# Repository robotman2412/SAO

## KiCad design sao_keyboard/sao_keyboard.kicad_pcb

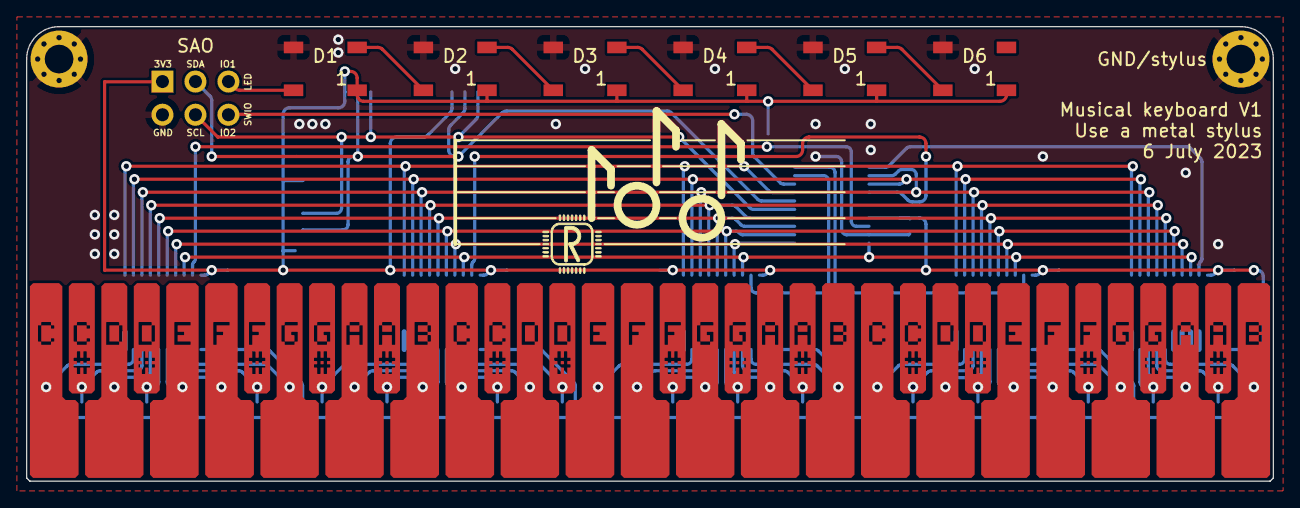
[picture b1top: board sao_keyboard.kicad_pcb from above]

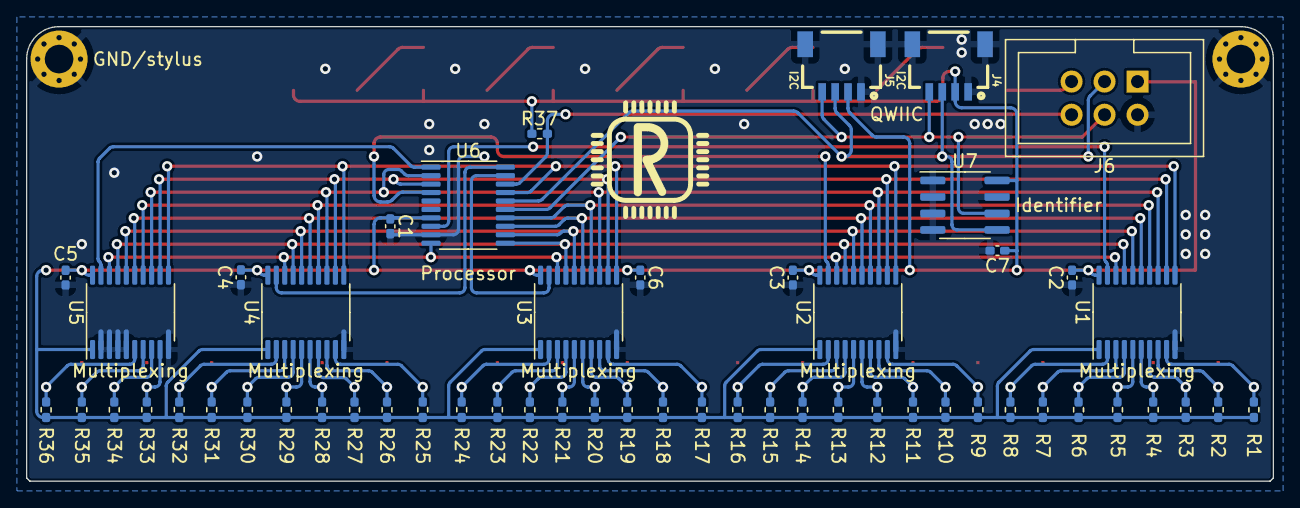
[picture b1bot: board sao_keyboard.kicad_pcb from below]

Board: 2 copper layers, 96.0 x 35.0 mm, 67 parts (54 on the bottom side), 60 nets.

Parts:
C1, C2, C3, C4, C5, C6, C7: 100n; C_0402_1005Metric_Pad0.74x0.62mm_HandSolder
D1, D2, D3, D4, D5, D6: WS2812B; LED_WS2812B_PLCC4_5.0x5.0mm_P3.2mm
G1: RobotMan2412_10mm
G2: RobotMan2412_5mm
H1, H2: MountingHole_Pad; MountingHole_2.2mm_M2_Pad_Via
J1, J2, J3: keyboard_32x15mm_p4mm_cu_label
J4, J5: I2C; 1X04_1MM_RA_GND
J6: sao_v2_addon_tht
R1, R2, R3, R4, R5, R6, R7, R8, R9, R10, R11, R12, R13, R14, R15, R16, R17, R18, R19, R20, R21, R22, R23, R24, R25, R26, R27, R28, R29, R30, R31, R32, R33, R34, R35, R36, R37: 1K; R_0402_1005Metric_Pad0.72x0.64mm_HandSolder
U1, U2, U3, U4, U5: 74LS245; TSSOP-20_4.4x6.5mm_P0.65mm
U6: CH32V003F4P6; TSSOP-20_4.4x6.5mm_P0.65mm
U7: 24LC00; SOIC-8_3.9x4.9mm_P1.27mm

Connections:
+3V3: C1.1, C2.1, C3.1, C4.1, C5.1, C6.1, C7.1, D1.1 (VDD), D2.1 (VDD), D3.1 (VDD), D4.1 (VDD), D5.1 (VDD), D6.1 (VDD), J4.2 (VCC), J5.2 (VCC), J6.1 (3V3), R1.1, R2.1, R3.1, R4.1, R5.1, R6.1, R7.1, R8.1, R9.1, R10.1, R11.1, R12.1, R13.1, R14.1, R15.1, R16.1, R17.1, R18.1, R19.1, R20.1, R21.1, R22.1, R23.1, R24.1, R25.1, R26.1, R27.1, R28.1, R29.1, R30.1, R31.1, R32.1, R33.1, R34.1, R35.1, R36.1, R37.1, U1.1 (A->B), U1.20 (VCC), U2.1 (A->B), U2.20 (VCC), U3.1 (A->B), U3.20 (VCC), U4.1 (A->B), U4.20 (VCC), U5.1 (A->B), U5.20 (VCC), U6.7 (VSS), U7.8 (VCC)
GND: C1.2, C2.2, C3.2, C4.2, C5.2, C6.2, C7.2, D1.3 (VSS), D2.3 (VSS), D3.3 (VSS), D4.3 (VSS), D5.3 (VSS), D6.3 (VSS), H1.1, H2.1, J4.1 (GND), J4.5, J4.6, J5.1 (GND), J5.5, J5.6, J6.2 (GND), U1.10 (GND), U2.10 (GND), U3.10 (GND), U4.10 (GND), U5.2 (A0), U5.3 (A1), U5.4 (A2), U5.5 (A3), U5.10 (GND), U6.9 (VDD), U7.1 (A0), U7.2 (A1), U7.3 (A2), U7.4 (GND), U7.7 (WP)
LED_DIN: D1.4 (DIN), J6.5 (IO1)
unnamed: D1.2 (DOUT), D2.4 (DIN)
unnamed: D2.2 (DOUT), D3.4 (DIN)
unnamed: D3.2 (DOUT), D4.4 (DIN)
unnamed: D4.2 (DOUT), D5.4 (DIN)
unnamed: D5.2 (DOUT), D6.4 (DIN)
SCL: J4.4 (SCL), J5.4 (SCL), J6.4 (SCL), U6.15 (PC5), U7.6 (SCL)
SDA: J4.3 (SDA), J5.3 (SDA), J6.3 (SDA), U6.16 (PC6), U7.5 (SDA)
SWIO: J6.6 (IO2), R37.2, U6.18 (PD1)
X0: U1.19 (CE), U6.8 (PD0)
X0Y0: J1.1 (C), R1.2, U1.9 (A7)
X0Y1: J1.2 (C#), R2.2, U1.8 (A6)
X0Y2: J1.3 (D), R3.2, U1.7 (A5)
X0Y3: J1.4 (D#), R4.2, U1.6 (A4)
X0Y4: J1.5 (E), R5.2, U1.5 (A3)
X0Y5: J1.6 (F), R6.2, U1.4 (A2)
X0Y6: J1.7 (F#), R7.2, U1.3 (A1)
X0Y7: J1.8 (G), R8.2, U1.2 (A0)
X1: U2.19 (CE), U6.4 (PD7)
X1Y0: J1.9 (G#), R9.2, U2.9 (A7)
X1Y1: J1.10 (A), R10.2, U2.8 (A6)
X1Y2: J1.11 (A#), R11.2, U2.7 (A5)
X1Y3: J1.12 (B), R12.2, U2.6 (A4)
X1Y4: J2.1 (C), R13.2, U2.5 (A3)
X1Y5: J2.2 (C#), R14.2, U2.4 (A2)
X1Y6: J2.3 (D), R15.2, U2.3 (A1)
X1Y7: J2.4 (D#), R16.2, U2.2 (A0)
X2: U3.19 (CE), U6.19 (PD2)
X2Y0: J2.5 (E), R17.2, U3.9 (A7)
X2Y1: J2.6 (F), R18.2, U3.8 (A6)
X2Y2: J2.7 (F#), R19.2, U3.7 (A5)
X2Y3: J2.8 (G), R20.2, U3.6 (A4)
X2Y4: J2.9 (G#), R21.2, U3.5 (A3)
X2Y5: J2.10 (A), R22.2, U3.4 (A2)
X2Y6: J2.11 (A#), R23.2, U3.3 (A1)
X2Y7: J2.12 (B), R24.2, U3.2 (A0)
X3: U4.19 (CE), U6.20 (PD3)
X3Y0: J3.1 (C), R25.2, U4.9 (A7)
X3Y1: J3.2 (C#), R26.2, U4.8 (A6)
X3Y2: J3.3 (D), R27.2, U4.7 (A5)
X3Y3: J3.4 (D#), R28.2, U4.6 (A4)
X3Y4: J3.5 (E), R29.2, U4.5 (A3)
X3Y5: J3.6 (F), R30.2, U4.4 (A2)
X3Y6: J3.7 (F#), R31.2, U4.3 (A1)
X3Y7: J3.8 (G), R32.2, U4.2 (A0)
X4: U5.19 (CE), U6.1 (PD4)
X4Y0: J3.9 (G#), R33.2, U5.9 (A7)
X4Y1: J3.10 (A), R34.2, U5.8 (A6)
X4Y2: J3.11 (A#), R35.2, U5.7 (A5)
X4Y3: J3.12 (B), R36.2, U5.6 (A4)
Y0: U1.11 (B7), U2.11 (B7), U3.11 (B7), U4.11 (B7), U5.11 (B7), U6.17 (PC7)
Y1: U1.12 (B6), U2.12 (B6), U3.12 (B6), U4.12 (B6), U5.12 (B6), U6.3 (PD6)
Y2: U1.13 (B5), U2.13 (B5), U3.13 (B5), U4.13 (B5), U5.13 (B5), U6.2 (PD5)
Y3: U1.14 (B4), U2.14 (B4), U3.14 (B4), U4.14 (B4), U5.14 (B4), U6.14 (PC4)
Y4: U1.15 (B3), U2.15 (B3), U3.15 (B3), U4.15 (B3), U5.15 (B3), U6.13 (PC3)
Y5: U1.16 (B2), U2.16 (B2), U3.16 (B2), U4.16 (B2), U5.16 (B2), U6.12 (PC2)
Y6: U1.17 (B1), U2.17 (B1), U3.17 (B1), U4.17 (B1), U5.17 (B1), U6.11 (PC1)
Y7: U1.18 (B0), U2.18 (B0), U3.18 (B0), U4.18 (B0), U5.18 (B0), U6.10 (PC0)

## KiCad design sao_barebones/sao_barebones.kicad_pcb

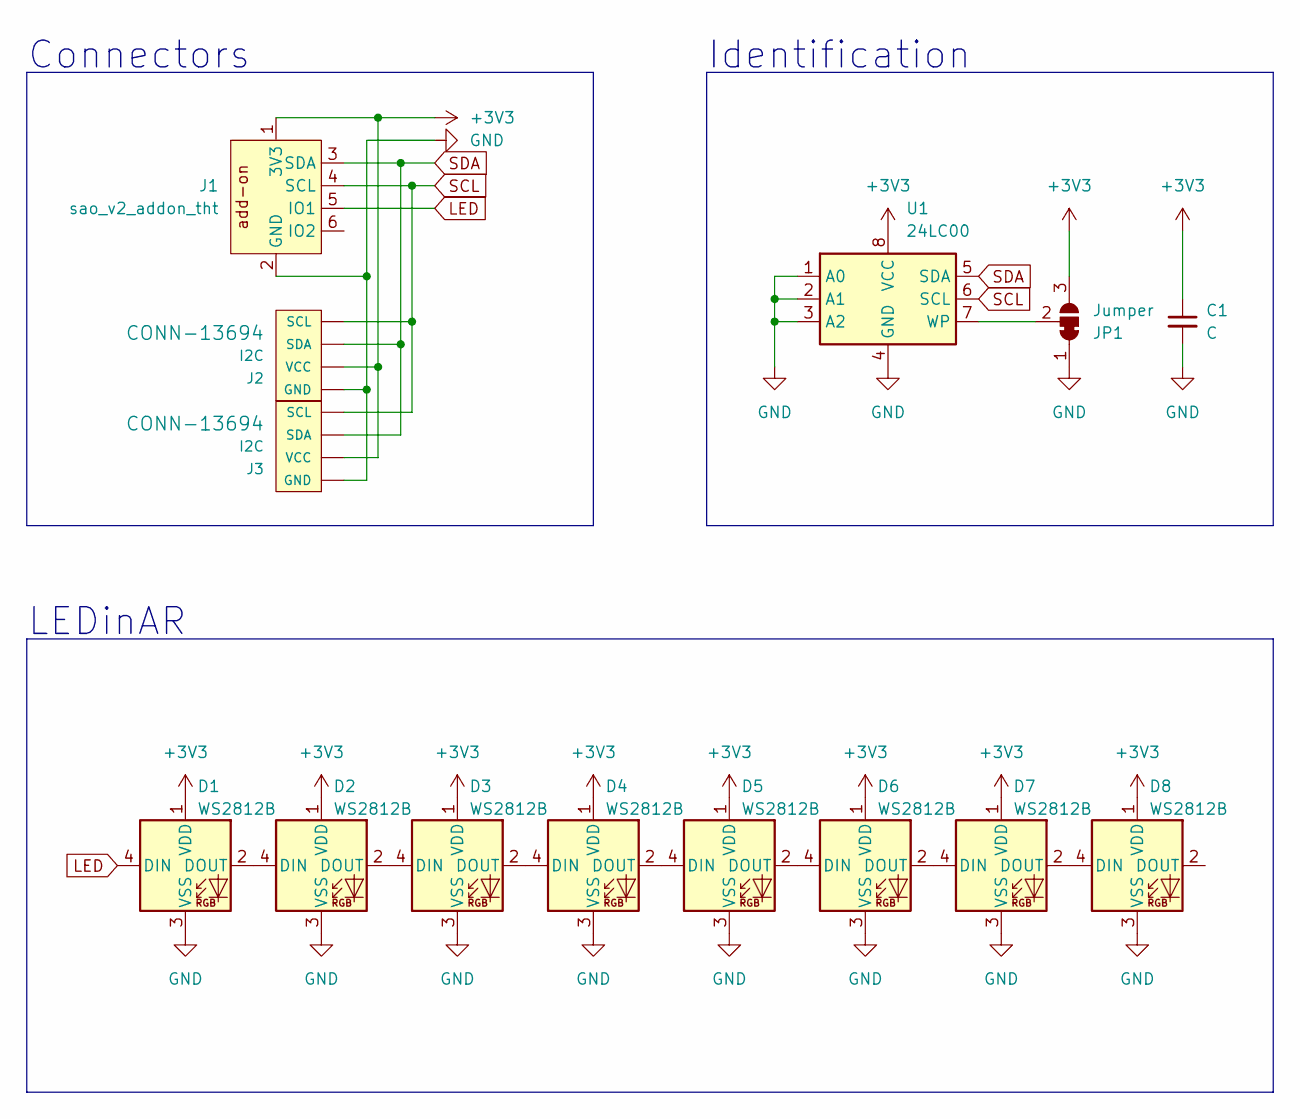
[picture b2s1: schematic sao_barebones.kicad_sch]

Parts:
C1: C; C_0402_1005Metric_Pad0.74x0.62mm_HandSolder
D1, D2, D3, D4, D5, D6, D7, D8: WS2812B; LED_WS2812B_PLCC4_5.0x5.0mm_P3.2mm
J1: sao_v2_addon_tht
J2, J3: I2C; 1X04_1MM_RA_GND; MPN SM04B-SRSS-TB; LCSC C160404
JP1: Jumper; SolderJumper-3_P1.3mm_Bridged12_RoundedPad1.0x1.5mm
U1: 24LC00; SOIC-8_3.9x4.9mm_P1.27mm

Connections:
+3V3: C1.1, D1.1 (VDD), D2.1 (VDD), D3.1 (VDD), D4.1 (VDD), D5.1 (VDD), D6.1 (VDD), D7.1 (VDD), D8.1 (VDD), J1.1 (3V3), J2.2 (VCC), J3.2 (VCC), JP1.3 (B), U1.8 (VCC)
GND: C1.2, D1.3 (VSS), D2.3 (VSS), D3.3 (VSS), D4.3 (VSS), D5.3 (VSS), D6.3 (VSS), D7.3 (VSS), D8.3 (VSS), J1.2 (GND), J2.1 (GND), J2.5, J2.6, J3.1 (GND), J3.5, J3.6, JP1.1 (A), U1.1 (A0), U1.2 (A1), U1.3 (A2), U1.4 (GND)
LED: D1.4 (DIN), J1.5 (IO1)
unnamed: D1.2 (DOUT), D2.4 (DIN)
unnamed: D2.2 (DOUT), D3.4 (DIN)
unnamed: D3.2 (DOUT), D4.4 (DIN)
unnamed: D4.2 (DOUT), D5.4 (DIN)
unnamed: D5.2 (DOUT), D6.4 (DIN)
unnamed: D6.2 (DOUT), D7.4 (DIN)
unnamed: D7.2 (DOUT), D8.4 (DIN)
unnamed: JP1.2 (C), U1.7 (WP)
SCL: J1.4 (SCL), J2.4 (SCL), J3.4 (SCL), U1.6 (SCL)
SDA: J1.3 (SDA), J2.3 (SDA), J3.3 (SDA), U1.5 (SDA)

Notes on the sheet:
Connectors
LEDinAR
Identification

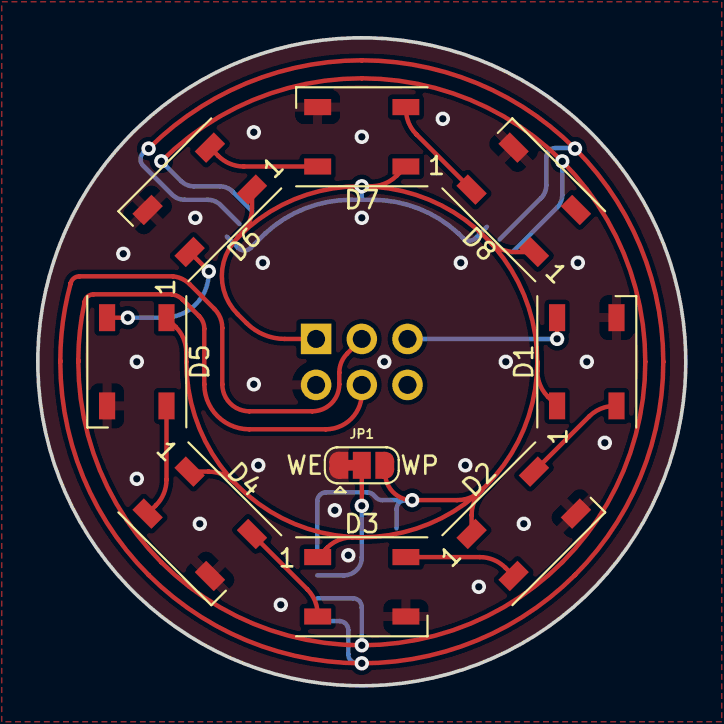
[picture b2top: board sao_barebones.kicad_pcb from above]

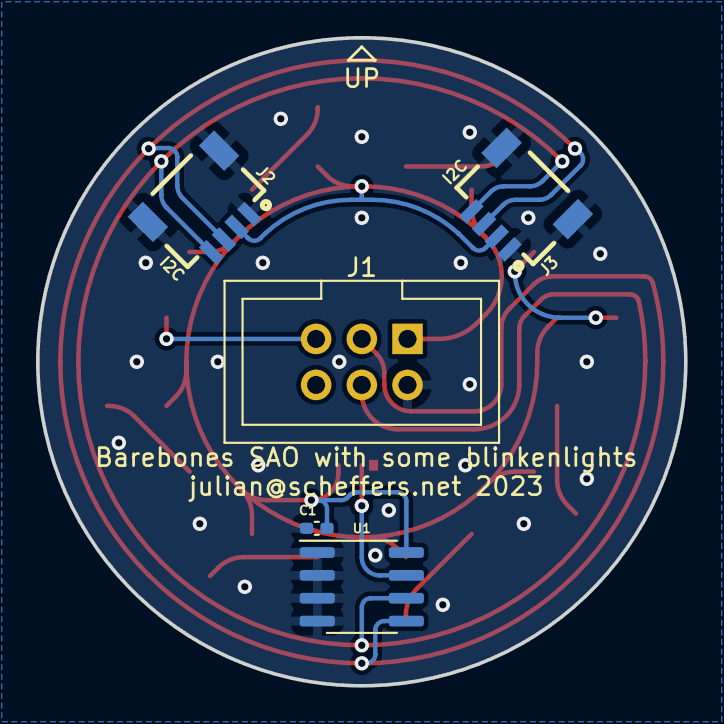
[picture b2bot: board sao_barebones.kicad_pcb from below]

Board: 2 copper layers, 36.0 x 36.0 mm, 15 parts (4 on the bottom side), 13 nets.

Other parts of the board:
G1: RobotMan2412_Mask_5mm

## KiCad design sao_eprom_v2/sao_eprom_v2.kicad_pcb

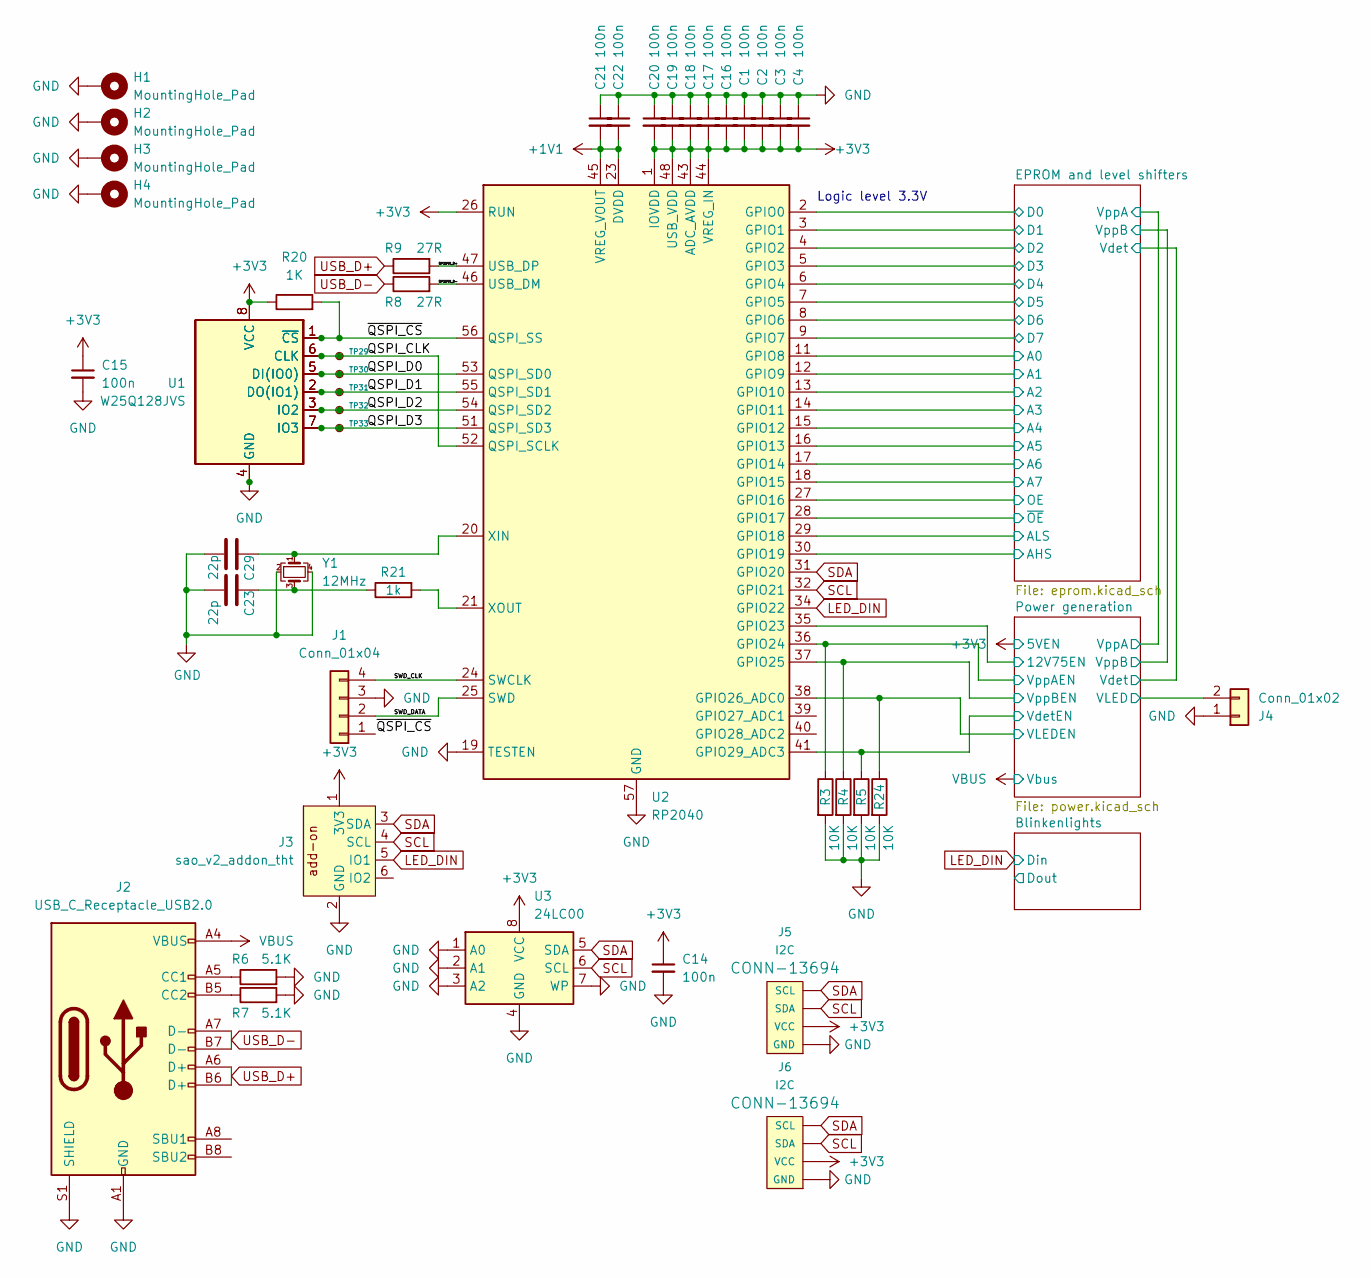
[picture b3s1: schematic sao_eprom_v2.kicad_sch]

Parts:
C1, C2, C3, C4, C14, C15, C16, C17, C18, C19, C20, C21, C22: 100n; C_0402_1005Metric_Pad0.74x0.62mm_HandSolder
C23, C29: 22p; C_0402_1005Metric_Pad0.74x0.62mm_HandSolder; Minimal voltage rating 10; Voltage rating 50; MPN TCC0402C0G220J500AT; LCSC C466226
H1, H2, H3, H4: MountingHole_Pad; MountingHole_2.2mm_M2_Pad_Via
J1: Conn_01x04; PinHeader_1x04_P2.54mm_Vertical
J2: USB_C_Receptacle_USB2.0; USB_C_Receptacle_G-Switch_GT-USB-7010ASV
J3: sao_v2_addon_tht
J4: Conn_01x02; PinHeader_1x02_P2.54mm_Vertical
J5, J6: I2C; 1X04_1MM_RA_GND; MPN SM04B-SRSS-TB; LCSC C160404
R3, R4, R5, R24: 10K; R_0402_1005Metric_Pad0.72x0.64mm_HandSolder
R6, R7: 5.1K; R_0402_1005Metric_Pad0.72x0.64mm_HandSolder
R8, R9: 27R; R_0402_1005Metric_Pad0.72x0.64mm_HandSolder
R20: 1K; R_0402_1005Metric_Pad0.72x0.64mm_HandSolder
R21: 1k; R_0402_1005Metric_Pad0.72x0.64mm_HandSolder; MPN 0402WGF1001TCE; LCSC C11702
TP29, TP30, TP31, TP32, TP33: TestPoint_Small; TestPoint_Pad_D1.0mm
U1: W25Q128JVS; SOIC-8_5.23x5.23mm_P1.27mm
U2: RP2040; QFN-56-1EP_7x7mm_P0.4mm_EP3.2x3.2mm
U3: 24LC00; SOIC-8_3.9x4.9mm_P1.27mm
U11: W25Q16JVUXIQ; PSON50P300X200X60-9N
Y1: 12MHz; Crystal_SMD_3225-4Pin_3.2x2.5mm; MPN S3212000181080; LCSC C390764

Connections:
+1V1: C21.2, C22.2, U2.23 (DVDD), U2.45 (VREG_VOUT), U2.50 (DVDD)
/EPROM and level shifters/A0: U2.11 (GPIO8); also elsewhere on the board
/EPROM and level shifters/A1: U2.12 (GPIO9); also elsewhere on the board
/EPROM and level shifters/A2: U2.13 (GPIO10); also elsewhere on the board
/EPROM and level shifters/A3: U2.14 (GPIO11); also elsewhere on the board
/EPROM and level shifters/A4: U2.15 (GPIO12); also elsewhere on the board
/EPROM and level shifters/A5: U2.16 (GPIO13); also elsewhere on the board
/EPROM and level shifters/A6: U2.17 (GPIO14); also elsewhere on the board
/EPROM and level shifters/A7: U2.18 (GPIO15); also elsewhere on the board
/EPROM and level shifters/AHS: U2.30 (GPIO19); also elsewhere on the board
/EPROM and level shifters/ALS: U2.29 (GPIO18); also elsewhere on the board
/EPROM and level shifters/D0: U2.2 (GPIO0); also elsewhere on the board
/EPROM and level shifters/D1: U2.3 (GPIO1); also elsewhere on the board
/EPROM and level shifters/D2: U2.4 (GPIO2); also elsewhere on the board
/EPROM and level shifters/D3: U2.5 (GPIO3); also elsewhere on the board
/EPROM and level shifters/D4: U2.6 (GPIO4); also elsewhere on the board
/EPROM and level shifters/D5: U2.7 (GPIO5); also elsewhere on the board
/EPROM and level shifters/D6: U2.8 (GPIO6); also elsewhere on the board
/EPROM and level shifters/D7: U2.9 (GPIO7); also elsewhere on the board
/EPROM and level shifters/OE: U2.27 (GPIO16); also elsewhere on the board
/EPROM and level shifters/~OE: U2.28 (GPIO17); also elsewhere on the board
/Power generation/12V75EN: U2.35 (GPIO23); also elsewhere on the board
/Power generation/VLED: J4.2; also elsewhere on the board
/Power generation/VLEDEN: R24.1, U2.38 (GPIO26_ADC0); also elsewhere on the board
/Power generation/VdetEN: R5.1, U2.41 (GPIO29_ADC3); also elsewhere on the board
/Power generation/VppAEN: R3.1, U2.36 (GPIO24); also elsewhere on the board
/Power generation/VppBEN: R4.1, U2.37 (GPIO25); also elsewhere on the board
/QSPI_CLK: TP29.1, U1.6 (CLK), U2.52 (QSPI_SCLK), U11.6 (CLK)
/QSPI_D0: TP30.1, U1.5 (DI(IO0)), U2.53 (QSPI_SD0), U11.5 (DI(IO0))
/QSPI_D1: TP31.1, U1.2 (DO(IO1)), U2.55 (QSPI_SD1), U11.2 (DO(IO1))
/QSPI_D2: TP32.1, U1.3 (IO2), U2.54 (QSPI_SD2), U11.3 (IO2)
/QSPI_D3: TP33.1, U1.7 (IO3), U2.51 (QSPI_SD3), U11.7 (IO3)
/RP2040_D+: R9.2, U2.47 (USB_DP)
/RP2040_D-: R8.2, U2.46 (USB_DM)
/SWD_CLK: J1.4, U2.24 (SWCLK)
/SWD_DATA: J1.2, U2.25 (SWD)
/~QSPI_CS: J1.1, R20.2, U1.1 (~CS), U2.56 (QSPI_SS), U11.1 (~CS)
GND: C1.1, C2.1, C3.1, C4.1, C14.2, C15.2, C16.1, C17.1, C18.1, C19.1, C20.1, C21.1, C22.1, C23.2, C29.2, H1.1, H2.1, H3.1, H4.1, J1.3, J2.A1 (GND), J2.A12 (GND), J2.B1 (GND), J2.B12 (GND), J2.S1 (SHIELD), J3.2 (GND), J4.1, J5.1 (GND), J5.5, J5.6, J6.1 (GND), J6.5, J6.6, R3.2, R4.2, R5.2, R6.2, R7.2, R24.2, U1.4 (GND), U2.19 (TESTEN), U2.57 (GND), U3.1 (A0), U3.2 (A1), U3.3 (A2), U3.4 (GND), U3.7 (WP), U11.4 (GND), Y1.2, Y1.4; also elsewhere on the board
unnamed: C23.1, R21.1, Y1.3
unnamed: J2.A5 (CC1), R6.1
unnamed: J2.B5 (CC2), R7.1
unnamed: C29.1, U2.20 (XIN), Y1.1
unnamed: R21.2, U2.21 (XOUT)
SCL: J3.4 (SCL), J5.3 (SDA), J6.3 (SDA), U2.32 (GPIO21), U3.6 (SCL)
SDA: J3.3 (SDA), J5.4 (SCL), J6.4 (SCL), U2.31 (GPIO20), U3.5 (SDA)
USB_D+: J2.A6 (D+), J2.B6 (D+), R9.1
USB_D-: J2.A7 (D-), J2.B7 (D-), R8.1
VBUS: J2.A4 (VBUS), J2.A9 (VBUS), J2.B4 (VBUS), J2.B9 (VBUS); also elsewhere on the board

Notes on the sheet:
Logic level 3.3V

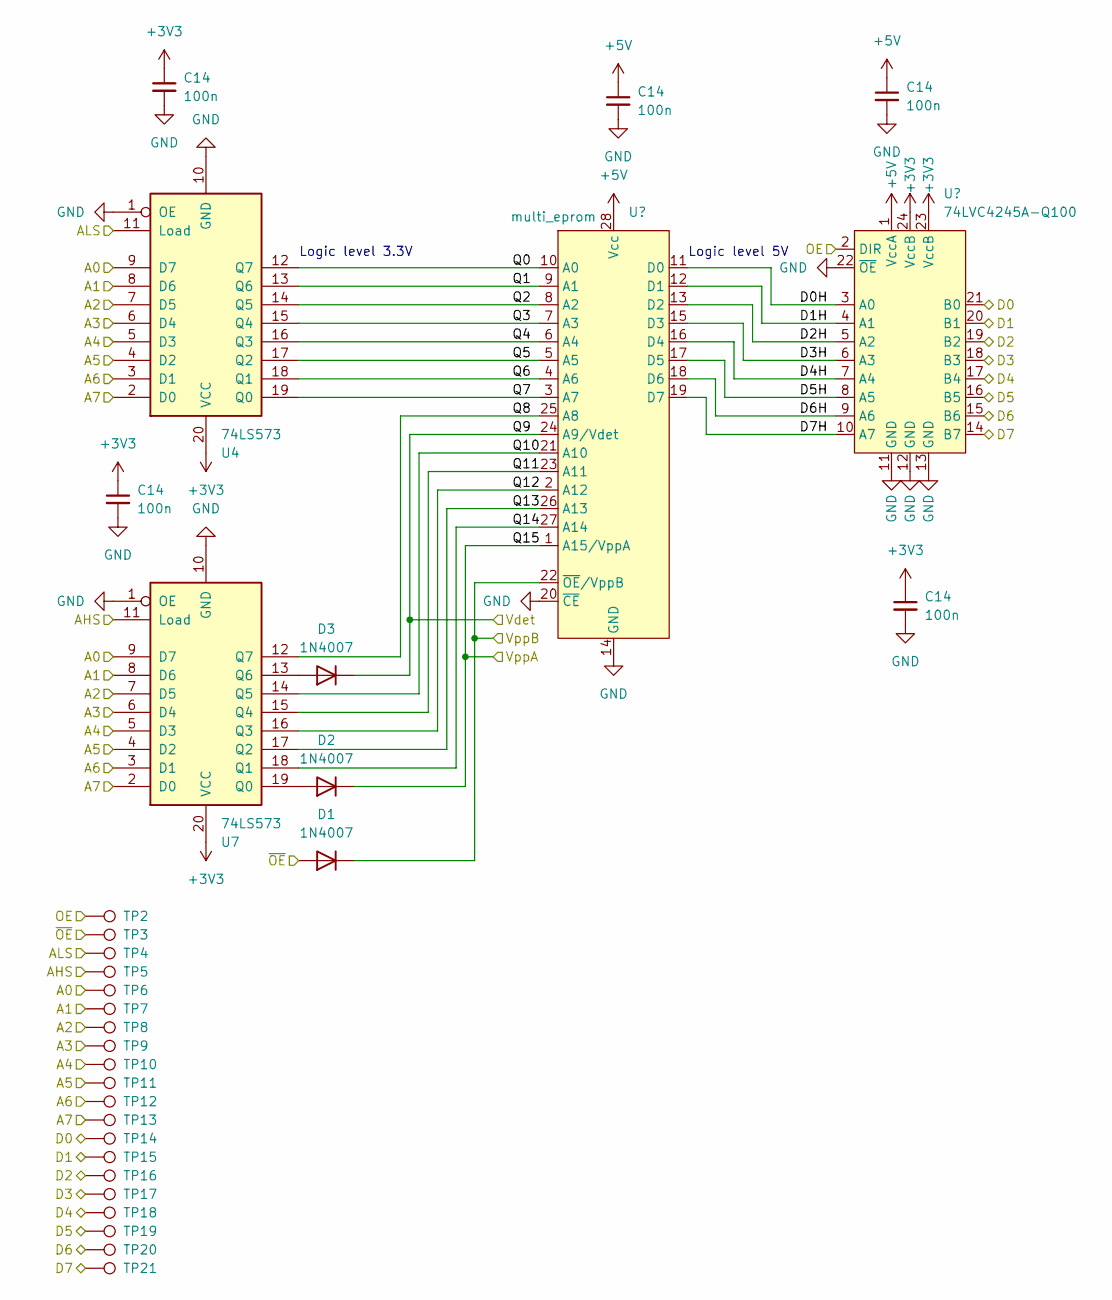
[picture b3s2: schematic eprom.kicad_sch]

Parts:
C14: 100n; C_0402_1005Metric_Pad0.74x0.62mm_HandSolder
D1, D2, D3: 1N4007; D_SOD-323_HandSoldering
TP2, TP3, TP4, TP5, TP6, TP7, TP8, TP9, TP10, TP11, TP12, TP13, TP14, TP15, TP16, TP17, TP18, TP19, TP20, TP21: TestPoint; TestPoint_Pad_D1.0mm
U4, U7: 74LS573; TSSOP-20_4.4x6.5mm_P0.65mm
U5: multi_eprom; DIP-28_W15.24mm_Socket
U6: 74LVC4245A-Q100; TSSOP-24_4.4x7.8mm_P0.65mm

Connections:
/EPROM and level shifters/A0: TP6.1, U4.9 (D7), U7.9 (D7); also elsewhere on the board
/EPROM and level shifters/A1: TP7.1, U4.8 (D6), U7.8 (D6); also elsewhere on the board
/EPROM and level shifters/A2: TP8.1, U4.7 (D5), U7.7 (D5); also elsewhere on the board
/EPROM and level shifters/A3: TP9.1, U4.6 (D4), U7.6 (D4); also elsewhere on the board
/EPROM and level shifters/A4: TP10.1, U4.5 (D3), U7.5 (D3); also elsewhere on the board
/EPROM and level shifters/A5: TP11.1, U4.4 (D2), U7.4 (D2); also elsewhere on the board
/EPROM and level shifters/A6: TP12.1, U4.3 (D1), U7.3 (D1); also elsewhere on the board
/EPROM and level shifters/A7: TP13.1, U4.2 (D0), U7.2 (D0); also elsewhere on the board
/EPROM and level shifters/AHS: TP5.1, U7.11 (Load); also elsewhere on the board
/EPROM and level shifters/ALS: TP4.1, U4.11 (Load); also elsewhere on the board
/EPROM and level shifters/D0: TP14.1, U6.21 (B0); also elsewhere on the board
/EPROM and level shifters/D0H: U5.11 (D0), U6.3 (A0)
/EPROM and level shifters/D1: TP15.1, U6.20 (B1); also elsewhere on the board
/EPROM and level shifters/D1H: U5.12 (D1), U6.4 (A1)
/EPROM and level shifters/D2: TP16.1, U6.19 (B2); also elsewhere on the board
/EPROM and level shifters/D2H: U5.13 (D2), U6.5 (A2)
/EPROM and level shifters/D3: TP17.1, U6.18 (B3); also elsewhere on the board
/EPROM and level shifters/D3H: U5.15 (D3), U6.6 (A3)
/EPROM and level shifters/D4: TP18.1, U6.17 (B4); also elsewhere on the board
/EPROM and level shifters/D4H: U5.16 (D4), U6.7 (A4)
/EPROM and level shifters/D5: TP19.1, U6.16 (B5); also elsewhere on the board
/EPROM and level shifters/D5H: U5.17 (D5), U6.8 (A5)
/EPROM and level shifters/D6: TP20.1, U6.15 (B6); also elsewhere on the board
/EPROM and level shifters/D6H: U5.18 (D6), U6.9 (A6)
/EPROM and level shifters/D7: TP21.1, U6.14 (B7); also elsewhere on the board
/EPROM and level shifters/D7H: U5.19 (D7), U6.10 (A7)
/EPROM and level shifters/OE: TP2.1, U6.2 (DIR); also elsewhere on the board
/EPROM and level shifters/Q0: U4.12 (Q7), U5.10 (A0)
/EPROM and level shifters/Q1: U4.13 (Q6), U5.9 (A1)
/EPROM and level shifters/Q2: U4.14 (Q5), U5.8 (A2)
/EPROM and level shifters/Q3: U4.15 (Q4), U5.7 (A3)
/EPROM and level shifters/Q4: U4.16 (Q3), U5.6 (A4)
/EPROM and level shifters/Q5: U4.17 (Q2), U5.5 (A5)
/EPROM and level shifters/Q6: U4.18 (Q1), U5.4 (A6)
/EPROM and level shifters/Q7: U4.19 (Q0), U5.3 (A7)
/EPROM and level shifters/Q8: U5.25 (A8), U7.12 (Q7)
/EPROM and level shifters/Q9: D3.1 (K), U5.24 (A9/Vdet); also elsewhere on the board
/EPROM and level shifters/Q10: U5.21 (A10), U7.14 (Q5)
/EPROM and level shifters/Q11: U5.23 (A11), U7.15 (Q4)
/EPROM and level shifters/Q12: U5.2 (A12), U7.16 (Q3)
/EPROM and level shifters/Q13: U5.26 (A13), U7.17 (Q2)
/EPROM and level shifters/Q14: U5.27 (A14), U7.18 (Q1)
/EPROM and level shifters/Q15: D2.1 (K), U5.1 (A15/VppA); also elsewhere on the board
/EPROM and level shifters/VppB: D1.1 (K), U5.22 (~OE/VppB); also elsewhere on the board
/EPROM and level shifters/~OE: D1.2 (A), TP3.1; also elsewhere on the board
GND: C14.2, U4.1 (OE), U4.10 (GND), U5.14 (GND), U5.20 (~CE), U6.11 (GND), U6.12 (GND), U6.13 (GND), U6.22 (~OE), U7.1 (OE), U7.10 (GND); also elsewhere on the board
unnamed: D2.2 (A), U7.19 (Q0)
unnamed: D3.2 (A), U7.13 (Q6)

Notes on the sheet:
Logic level 5V
Logic level 3.3V

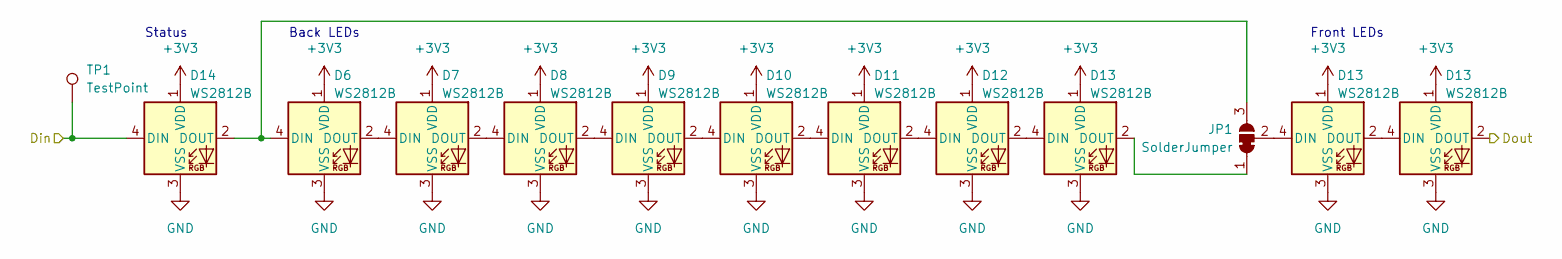
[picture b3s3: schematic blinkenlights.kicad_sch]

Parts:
D6, D7, D8, D9, D10, D11, D12, D13, D14: WS2812B; LED_WS2812B_PLCC4_5.0x5.0mm_P3.2mm
JP1: SolderJumper; SolderJumper-3_P1.3mm_Bridged2Bar12_Pad1.0x1.5mm
TP1: TestPoint; TestPoint_Pad_D1.0mm

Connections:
GND: D6.3 (VSS), D7.3 (VSS), D8.3 (VSS), D9.3 (VSS), D10.3 (VSS), D11.3 (VSS), D12.3 (VSS), D13.3 (VSS), D14.3 (VSS); also elsewhere on the board
unnamed: D7.2 (DOUT), D8.4 (DIN)
unnamed: D8.2 (DOUT), D9.4 (DIN)
unnamed: D9.2 (DOUT), D10.4 (DIN)
unnamed: D10.2 (DOUT), D11.4 (DIN)
unnamed: D11.2 (DOUT), D12.4 (DIN)

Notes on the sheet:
Back LEDs
Status
Front LEDs

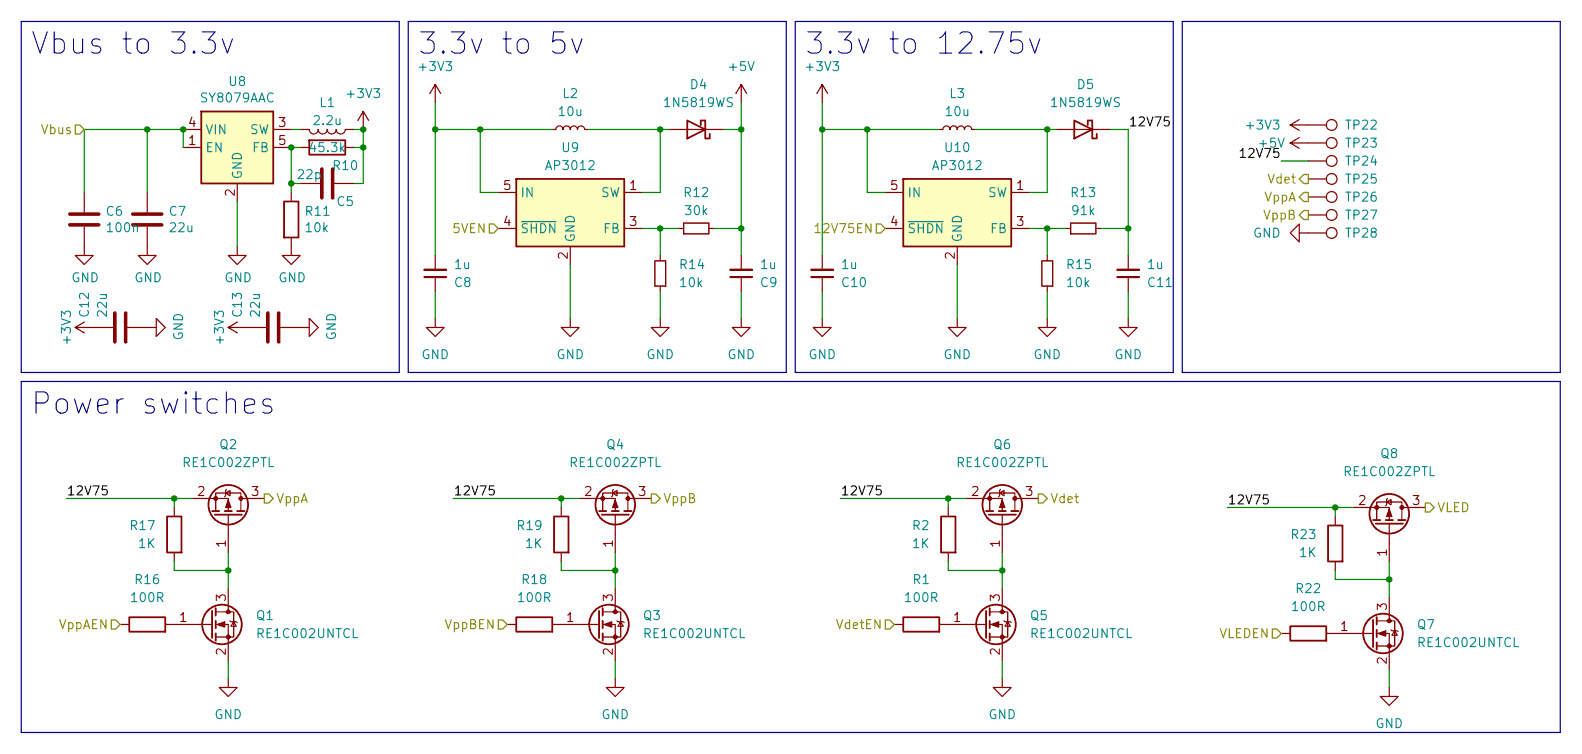
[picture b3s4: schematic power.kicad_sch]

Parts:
C5: 22p; C_0402_1005Metric_Pad0.74x0.62mm_HandSolder; Minimal voltage rating 10; Voltage rating 50; MPN TCC0402C0G220J500AT; LCSC C466226
C6: 100n; C_0402_1005Metric_Pad0.74x0.62mm_HandSolder; Minimal voltage rating 10; Voltage rating 50; MPN CL05B104KB54PNC; LCSC C307331
C7, C12, C13: 22u; C_0805_2012Metric_Pad1.18x1.45mm_HandSolder; Minimal voltage rating 10; Voltage rating 25; MPN CL21A226MAYNNNE; LCSC C602037
C8, C9, C10, C11: 1u; C_0603_1608Metric_Pad1.08x0.95mm_HandSolder
D4, D5: 1N5819WS; D_SOD-323_HandSoldering
L1: 2.2u; L_0805_2012Metric_Pad1.15x1.40mm_HandSolder; MPN MCS20FC-2R2MHC; LCSC C375944
L2, L3: 10u; L_0805_2012Metric_Pad1.15x1.40mm_HandSolder; Part CSME0418D-100M-LRH
Q1, Q3, Q5, Q7: RE1C002UNTCL; SOT-416
Q2, Q4, Q6, Q8: RE1C002ZPTL; SOT-416
R1, R16, R18, R22: 100R; R_0402_1005Metric_Pad0.72x0.64mm_HandSolder
R2, R17, R19, R23: 1K; R_0402_1005Metric_Pad0.72x0.64mm_HandSolder
R10: 45.3k; R_0402_1005Metric_Pad0.72x0.64mm_HandSolder; MPN 0402WGF4532TCE; LCSC C26980
R11: 10k; R_0402_1005Metric_Pad0.72x0.64mm_HandSolder; MPN 0402WGF1002TCE; LCSC C25744
R12: 30k; R_0402_1005Metric_Pad0.72x0.64mm_HandSolder
R13: 91k; R_0402_1005Metric_Pad0.72x0.64mm_HandSolder
R14, R15: 10k; R_0402_1005Metric_Pad0.72x0.64mm_HandSolder
TP22, TP23, TP24, TP25, TP26, TP27, TP28: TestPoint; TestPoint_Pad_D1.0mm
U8: SY8079AAC; SOT-23-5; MPN SY8079AAC; LCSC C133751
U9, U10: AP3012; SOT-23-5

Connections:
/EPROM and level shifters/Q9: Q6.3 (D), TP25.1; also elsewhere on the board
/EPROM and level shifters/Q15: Q2.3 (D), TP26.1; also elsewhere on the board
/EPROM and level shifters/VppB: Q4.3 (D), TP27.1; also elsewhere on the board
/Power generation/12V75: C11.2, D5.1 (K), Q2.2 (S), Q4.2 (S), Q6.2 (S), Q8.2 (S), R2.1, R13.2, R17.1, R19.1, R23.1, TP24.1
/Power generation/12V75EN: U10.4 (~SHDN); also elsewhere on the board
/Power generation/VLED: Q8.3 (D); also elsewhere on the board
/Power generation/VLEDEN: R22.1; also elsewhere on the board
/Power generation/VdetEN: R1.1; also elsewhere on the board
/Power generation/VppAEN: R16.1; also elsewhere on the board
/Power generation/VppBEN: R18.1; also elsewhere on the board
GND: C6.2, C7.2, C8.1, C9.1, C10.1, C11.1, C12.2, C13.2, Q1.2 (S), Q3.2 (S), Q5.2 (S), Q7.2 (S), R11.2, R14.1, R15.1, TP28.1, U8.2 (GND), U9.2 (GND), U10.2 (GND); also elsewhere on the board
unnamed: D4.2 (A), L2.2, U9.1 (SW)
unnamed: D5.2 (A), L3.2, U10.1 (SW)
unnamed: Q1.3 (D), Q2.1 (G), R17.2
unnamed: Q1.1 (G), R16.2
unnamed: Q3.3 (D), Q4.1 (G), R19.2
unnamed: Q3.1 (G), R18.2
unnamed: Q5.3 (D), Q6.1 (G), R2.2
unnamed: Q5.1 (G), R1.2
unnamed: Q7.3 (D), Q8.1 (G), R23.2
unnamed: Q7.1 (G), R22.2
unnamed: C5.2, R10.2, R11.1, U8.5 (FB)
unnamed: L1.2, U8.3 (SW)
unnamed: R12.1, R14.2, U9.3 (FB)
unnamed: R13.1, R15.2, U10.3 (FB)
VBUS: C6.1, C7.1, U8.1 (EN), U8.4 (VIN); also elsewhere on the board

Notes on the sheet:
3.3v to 12.75v
3.3v to 5v
Power switches
Vbus to 3.3v

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
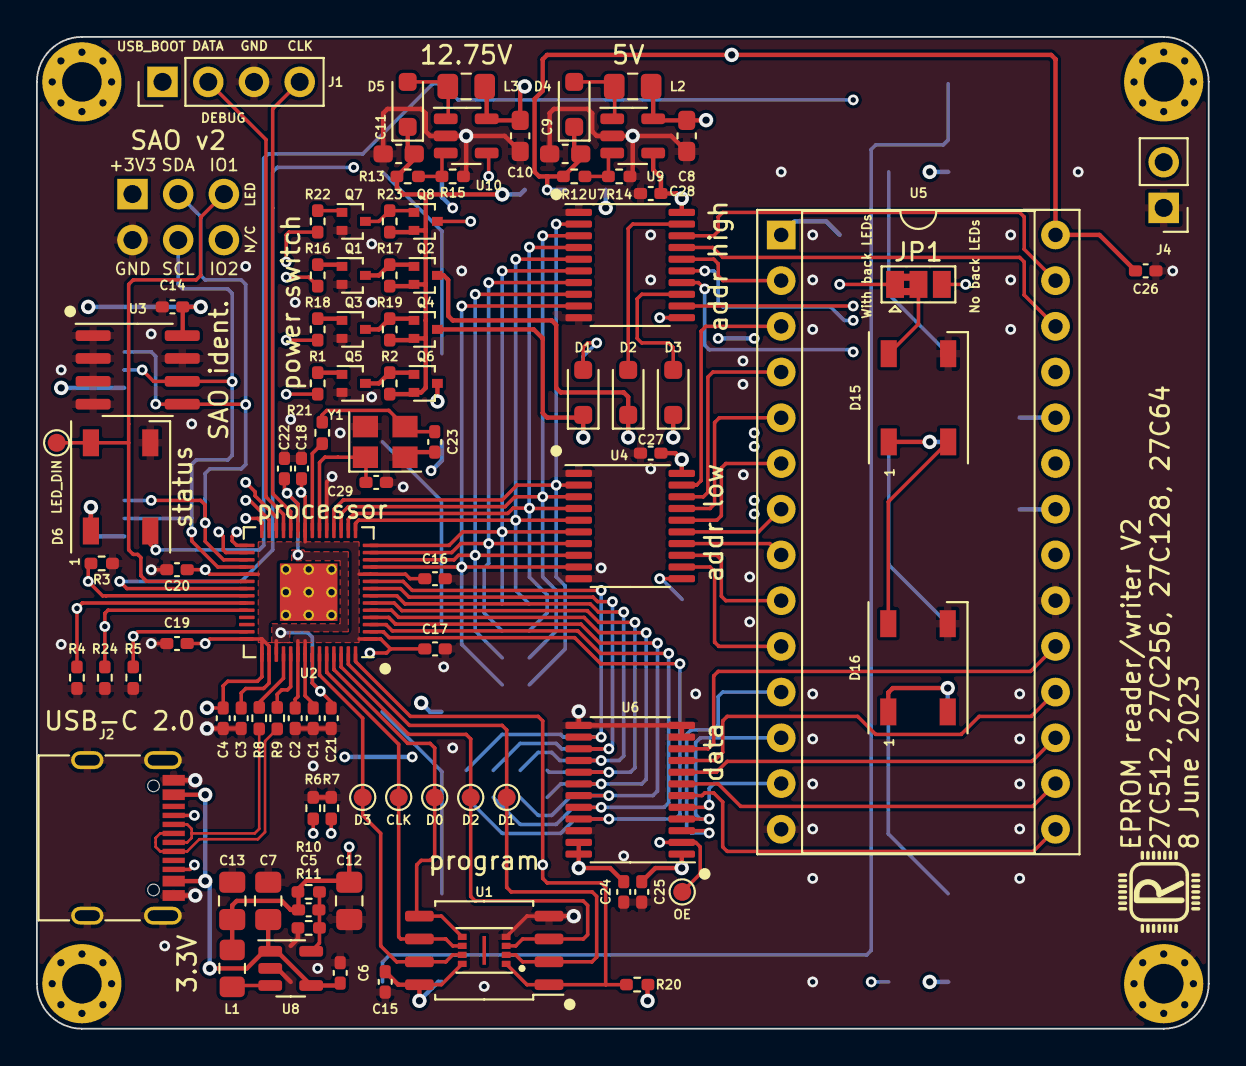
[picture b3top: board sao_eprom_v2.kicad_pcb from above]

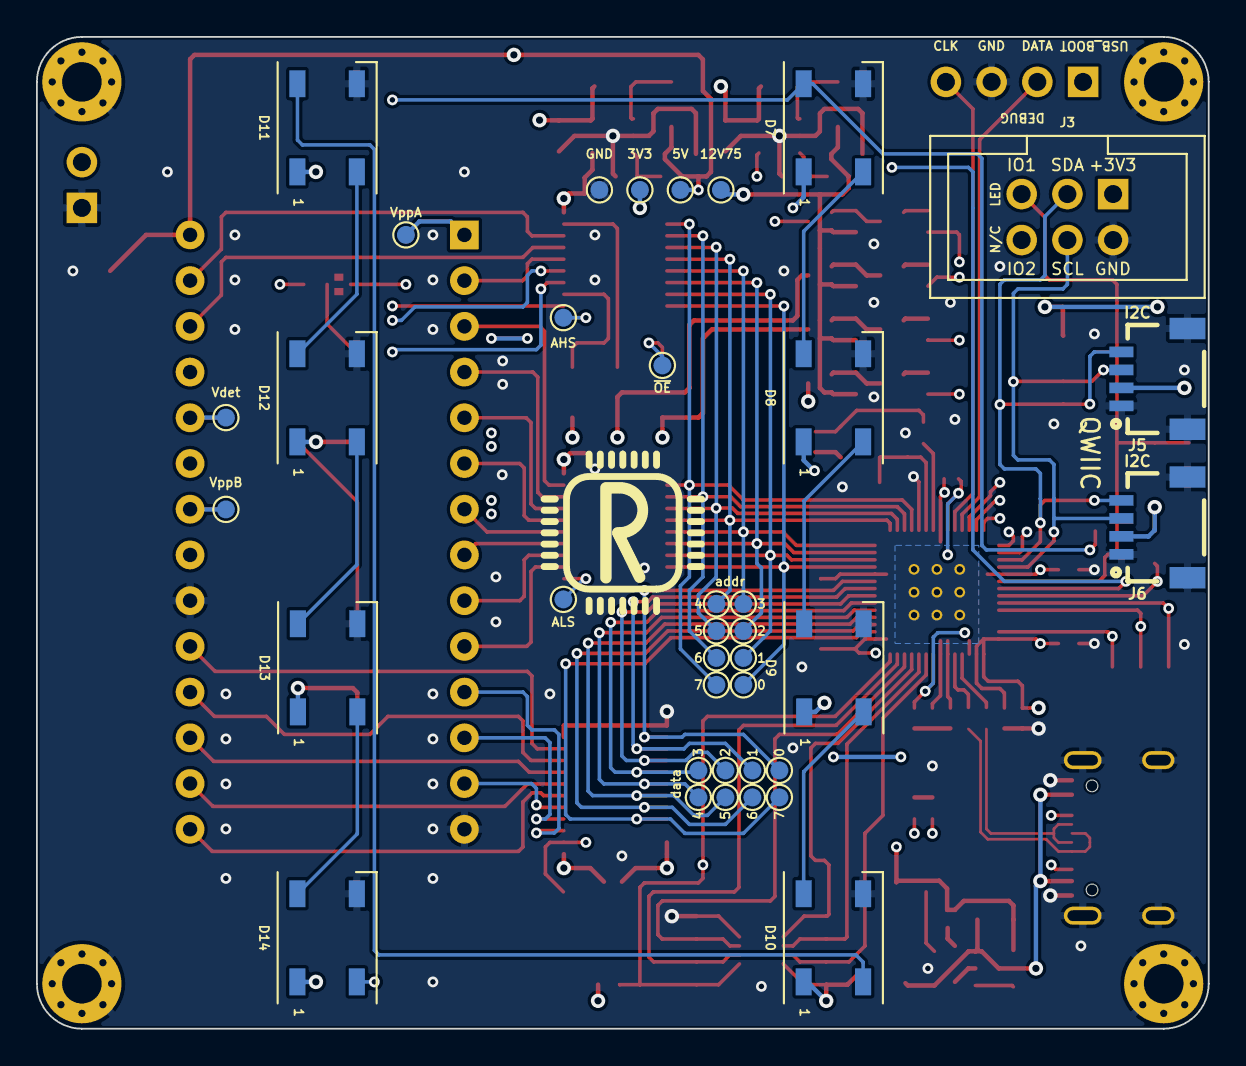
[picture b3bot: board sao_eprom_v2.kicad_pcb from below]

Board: 4 copper layers, 65.1 x 55.1 mm, 136 parts (36 on the bottom side), 104 nets.

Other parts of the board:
C24, C25, C26, C27, C28: 100n; C_0402_1005Metric_Pad0.74x0.62mm_HandSolder
D15, D16: WS2812B; LED_WS2812B_PLCC4_5.0x5.0mm_P3.2mm

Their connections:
GND: C24.2, C25.2, C26.2, C27.2, C28.2, D15.3 (VSS), D16.3 (VSS); also elsewhere on the board
unnamed: D15.2 (DOUT), D16.4 (DIN)
